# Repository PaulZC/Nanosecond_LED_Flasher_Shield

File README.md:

# Nanosecond LED Flasher Shield
 
A nanosecond LED flasher which provides digital control of both pulse width and LED current. Designed to aid
photomultiplier detector characterisation.

The LED is driven by the new [LMG1025 from Texas Instruments](http://www.ti.com/product/LMG1025-Q1).
Designed for automotive LIDAR applications, this gate driver has typical rise and fall times of 650ps
and 850ps and can produce 5V pulse widths as short as 1.25ns.

The pulse width is controlled by a [Maxim Integrated DS1023S-25+](https://www.maximintegrated.com/en/products/analog/clock-generation-distribution/DS1023.html)
programmable timing element which can produce digitally-adjustable pulse widths of 0 to ~64ns in 0.25ns increments.

The LED current is set by five surface mount resistors connected in series, four of which can be shorted
out by [Toshiba TLP3475 photorelays](https://toshiba.semicon-storage.com/ap-en/semiconductor/product/optoelectronics/photorelay-mosfet-output/detail.TLP3475.html)
allowing the LED current to be adjusted digitally in 16 increments.

The shield also uses a [u-blox MAX-M8Q GNSS module](https://www.u-blox.com/en/product/max-m8-series) as a
signal generator to dictate the flash rate. The flash rate can be set to any frequency between 0.25Hz
and 10MHz.

The shield is designed to be mounted on a [5V ATmega328 Arduino Uno or similar](https://www.sparkfun.com/products/13975).
(Please note that the shield requires 5V I/O signals for correct operation and will not work if mounted
on a 3.3V Arduino Zero or similar.)

## Example Performance

In the image below:
- the yellow trace shows the anode voltage of a Bivar UV3TZ-400-15 UV LED being driven by the shield at maximum brightness (equivalent series resistance approx. 14 ohms) (1V per division)
- the green trace shows the corresponding fast output of a SensL J-series silicon photomultiplier (50mV per division)
- the timebase is 2 nsec per division

The overlapping yellow traces show the LED pulse width being increased in 0.25 nsec increments. The corresponding green traces show how the peak output of
the SiPM increases in line with the LED pulse width and the number of photons emitted during each pulse.

## Repository Contents

- **/Documentation** - Documentation for the hardware and software
- **/Hardware** - BOM, schematic and Eagle PCB design files
- **/Software** - Arduino code
- **LICENSE.md** contains the licence information

## Documentation

- [Hardware overview](https://github.com/PaulZC/Nanosecond_LED_Flasher_Shield/blob/master/Documentation/Hardware/README.md): an overview of the hardware
- [Software user guide](https://github.com/PaulZC/Nanosecond_LED_Flasher_Shield/blob/master/Documentation/Software/README.md): a user guide for the Arduino code

Enjoy!

**_Paul_**

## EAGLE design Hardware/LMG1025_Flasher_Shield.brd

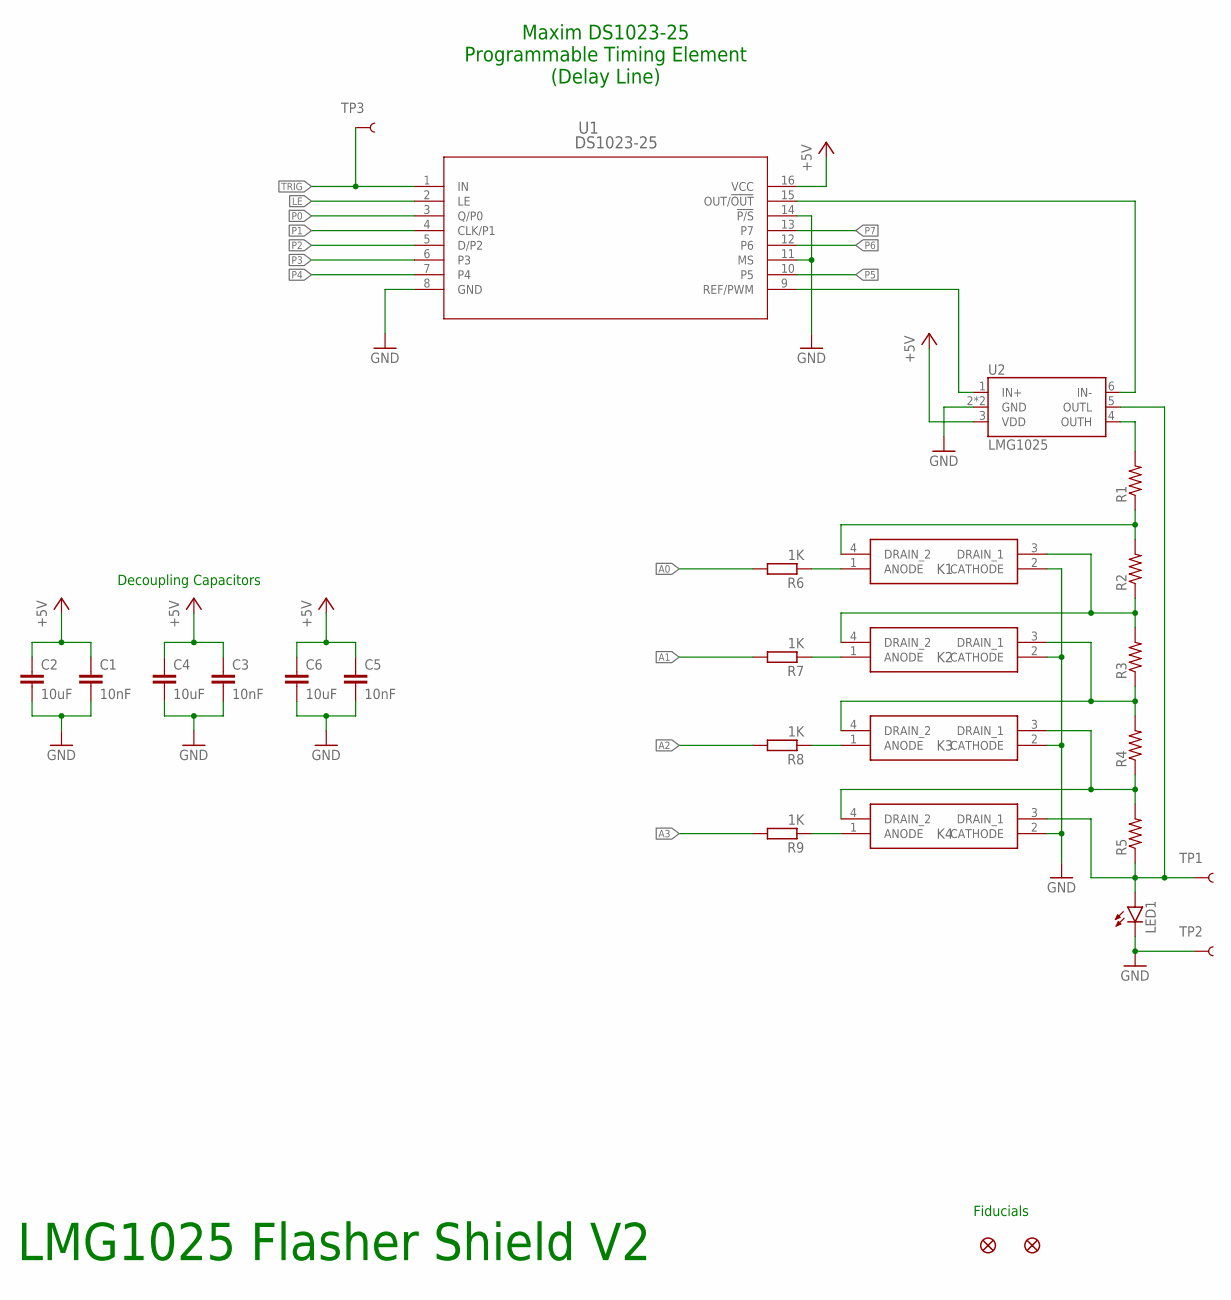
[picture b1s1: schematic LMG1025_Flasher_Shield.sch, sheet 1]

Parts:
C1, C3, C5: 10nF; C0805
C2, C4, C6: 10uF; C0805
FD1, FD2: FIDUCIAL1X2; FIDUCIAL-1X2
K1, K2, K3, K4: TLP3475R(TP,F; TLP3475RTPF
LED1: LED3MM
R1, R2, R3, R4, R5: RESISTOR0805-RES; 0805
R6, R7, R8, R9: 1K; R0603
TP1, TP2, TP3: TEST-POINTPOGO_PTH; 1X01_NO_SILK
U1: DS1023-25; 21-0042B_16
U2: LMG1025

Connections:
+5V: C1.1, C2.1, C3.1, C4.1, C5.1, C6.1, U1.16 (VCC), U2.3 (VDD); also elsewhere on the board
A0: R6.2; also elsewhere on the board
A1: R7.2; also elsewhere on the board
A2: R8.2; also elsewhere on the board
A3: R9.2; also elsewhere on the board
GND: C1.2, C2.2, C3.2, C4.2, C5.2, C6.2, K1.2 (CATHODE), K2.2 (CATHODE), K3.2 (CATHODE), K4.2 (CATHODE), LED1.K (C), TP2.1, U1.8 (GND), U1.11 (MS), U1.14 (!P/S), U2.2 (GND), U2.PAD (GND); also elsewhere on the board
LE: U1.2 (LE); also elsewhere on the board
unnamed: K1.4 (DRAIN_2), R1.1, R2.2
unnamed: K1.3 (DRAIN_1), K2.4 (DRAIN_2), R2.1, R3.2
unnamed: K4.3 (DRAIN_1), LED1.A, R5.1, TP1.1, U2.5 (OUTL)
unnamed: K2.3 (DRAIN_1), K3.4 (DRAIN_2), R3.1, R4.2
unnamed: K3.3 (DRAIN_1), K4.4 (DRAIN_2), R4.1, R5.2
unnamed: R1.2, U2.4 (OUTH)
unnamed: K1.1 (ANODE), R6.1
unnamed: K2.1 (ANODE), R7.1
unnamed: K3.1 (ANODE), R8.1
unnamed: K4.1 (ANODE), R9.1
unnamed: U1.9 (REF/PWM), U2.1 (IN+)
unnamed: U1.15 (OUT/!OUT), U2.6 (IN-)
P0: U1.3 (Q/P0); also elsewhere on the board
P1: U1.4 (CLK/P1); also elsewhere on the board
P2: U1.5 (D/P2); also elsewhere on the board
P3: U1.6 (P3); also elsewhere on the board
P4: U1.7 (P4); also elsewhere on the board
P5: U1.10 (P5); also elsewhere on the board
P6: U1.12 (P6); also elsewhere on the board
P7: U1.13 (P7); also elsewhere on the board
TRIG: TP3.1, U1.1 (IN); also elsewhere on the board

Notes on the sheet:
LMG1025 Flasher Shield V2
Fiducials
Decoupling Capacitors
Maxim DS1023-25 Programmable Timing Element (Delay Line)

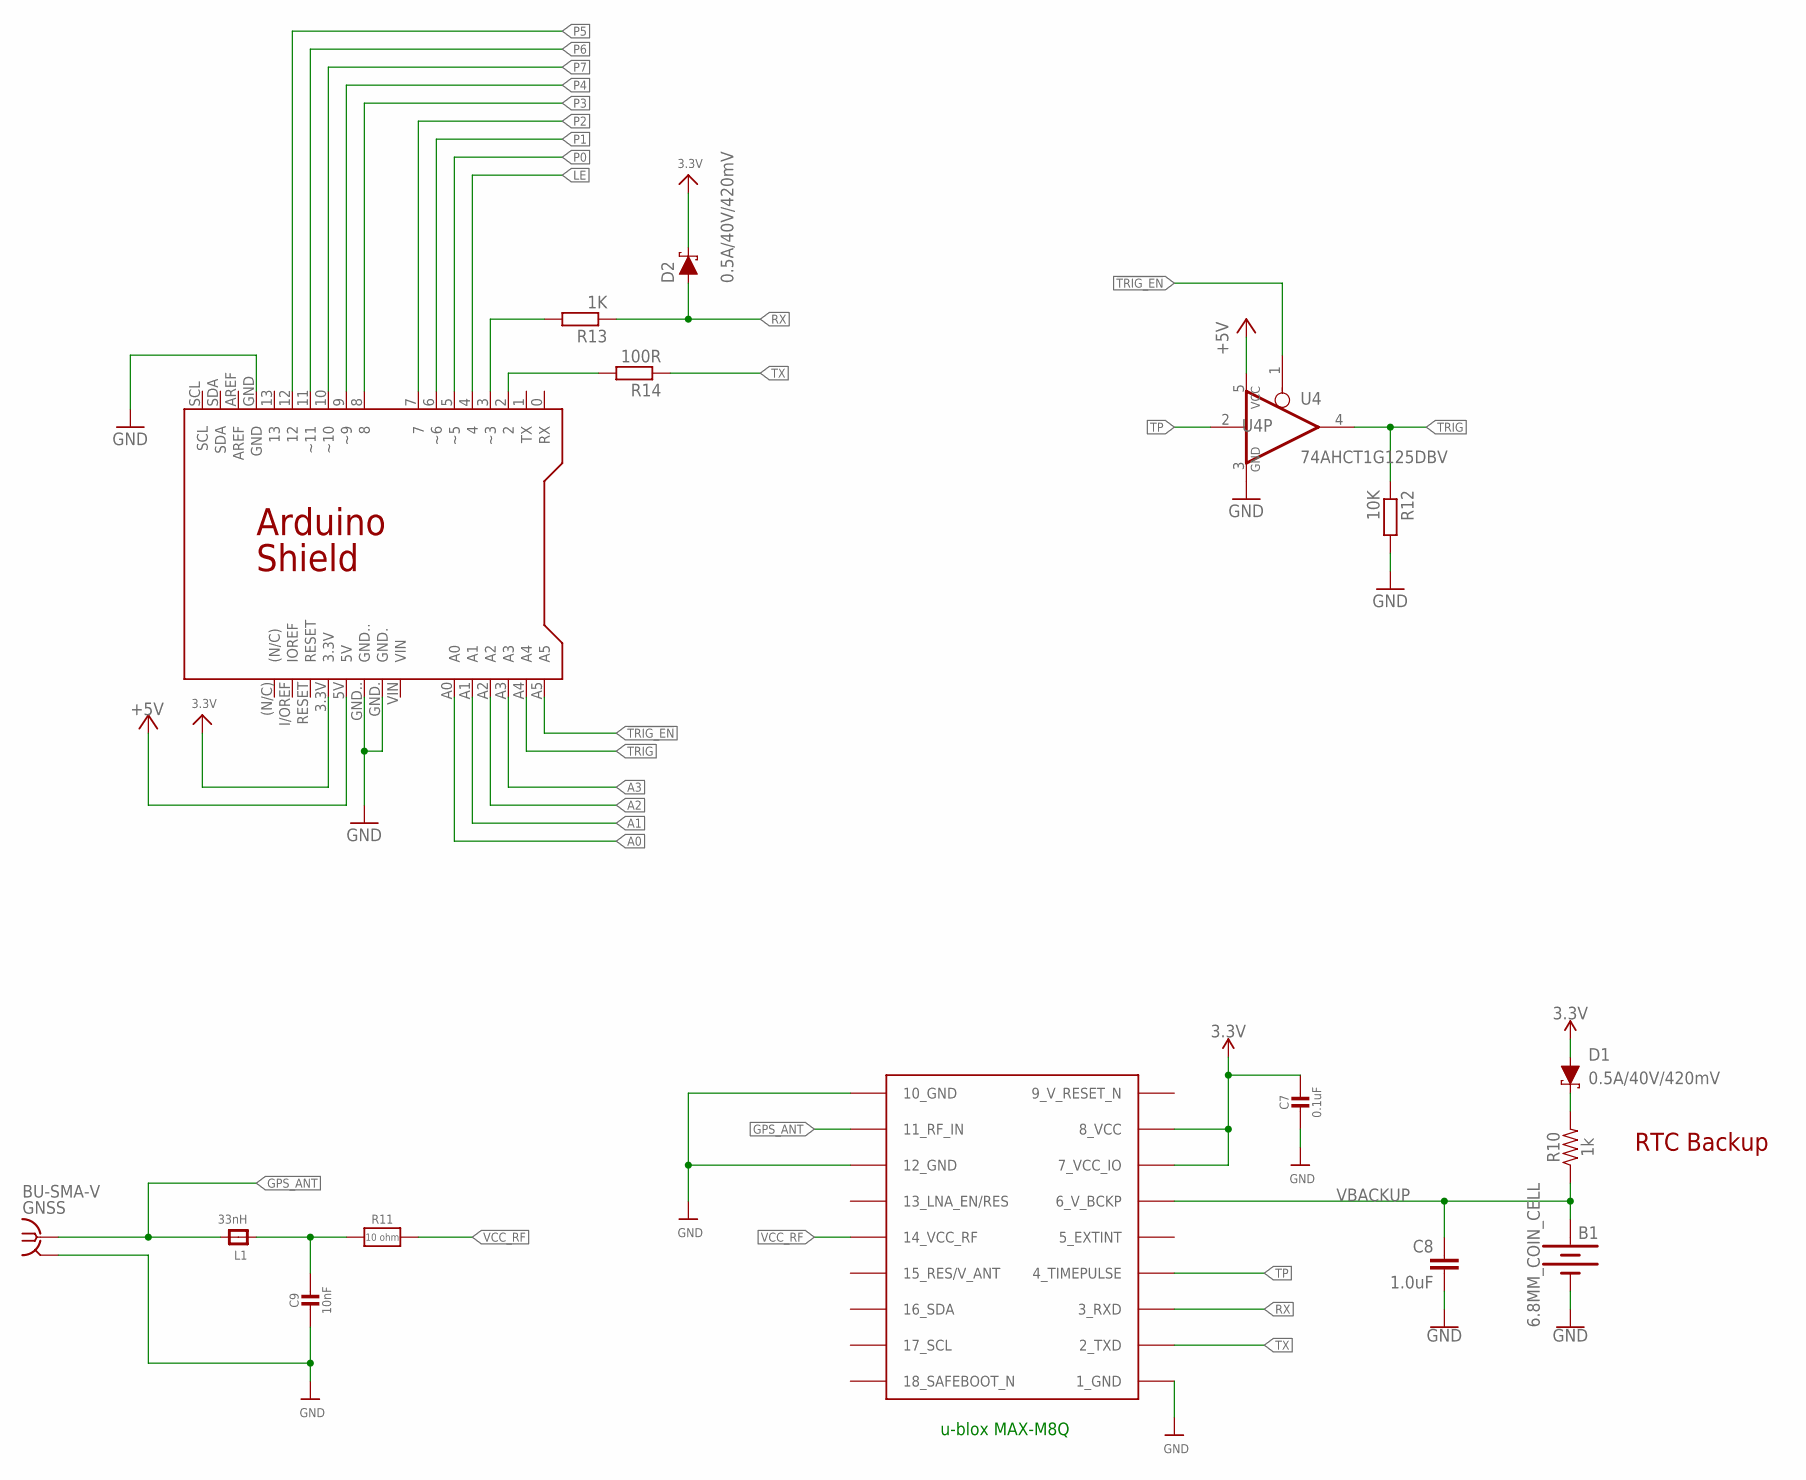
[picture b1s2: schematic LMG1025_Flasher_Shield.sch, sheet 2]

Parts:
B1: 6.8MM_COIN_CELL; BATTCON-6.8MM
C7: 0.1uF; 0805-NO
C8: 1.0uF; 0603
C9: 10nF; 0805-NO
D1, D2: 0.5A/40V/420mV; SOD-323
GNSS: BU-SMA-V
L1: 33nH; 0805-NO
PCB1: CHEC_LED_DRIVER_SHIELD
R10: 1k; 0603@1
R11: 10 ohm; 0805-NO
R12: 10K; R0603
R13: 1K; R0603
R14: 100R; R0603
U3: MAX-M8
U4: 74AHCT1G125DBV; SOT23-5

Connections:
3.3V: C7.1, D1.A, D2.C, PCB1.3.3V, U3.7_VCC_IO, U3.8_VCC
9_V_RESET_N: U3.9_RESET_N (9_V_RESET_N)
!TRIG_EN: PCB1.A5, U4.1 (OE)
+5V: PCB1.5V, U4.5 (VCC); also elsewhere on the board
A0: PCB1.A0; also elsewhere on the board
A1: PCB1.A1; also elsewhere on the board
A2: PCB1.A2; also elsewhere on the board
A3: PCB1.A3; also elsewhere on the board
GND: B1.-, C7.2, C8.2, C9.2, GNSS.2, GNSS.3 (2), GNSS.4 (2), GNSS.5 (2), PCB1.GND, PCB1.GND., PCB1.GND.., R12.2, U3.1_GND, U3.10_GND, U3.12_GND, U4.3 (GND); also elsewhere on the board
GPS_ANT: GNSS.1, L1.2, U3.11_RF_IN
LE: PCB1.4; also elsewhere on the board
unnamed: PCB1.3 (~3), R13.2
unnamed: C9.1, L1.1, R11.1
unnamed: D1.C, R10.2
unnamed: PCB1.2, R14.2
P0: PCB1.5 (~5); also elsewhere on the board
P1: PCB1.6 (~6); also elsewhere on the board
P2: PCB1.7; also elsewhere on the board
P3: PCB1.8; also elsewhere on the board
P4: PCB1.9 (~9); also elsewhere on the board
P5: PCB1.12; also elsewhere on the board
P6: PCB1.11 (~11); also elsewhere on the board
P7: PCB1.10 (~10); also elsewhere on the board
RX: D2.A, R13.1, U3.3_RXD
TP: U3.4_TIMEPULSE, U4.2 (I)
TRIG: PCB1.A4, R12.1, U4.4 (O); also elsewhere on the board
TX: R14.1, U3.2_TXD
VBACKUP: B1.+, C8.1, R10.1, U3.6_V_BCKP
VCC_RF: R11.2, U3.14_VCC_RF

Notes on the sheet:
u-blox MAX-M8Q
RTC Backup

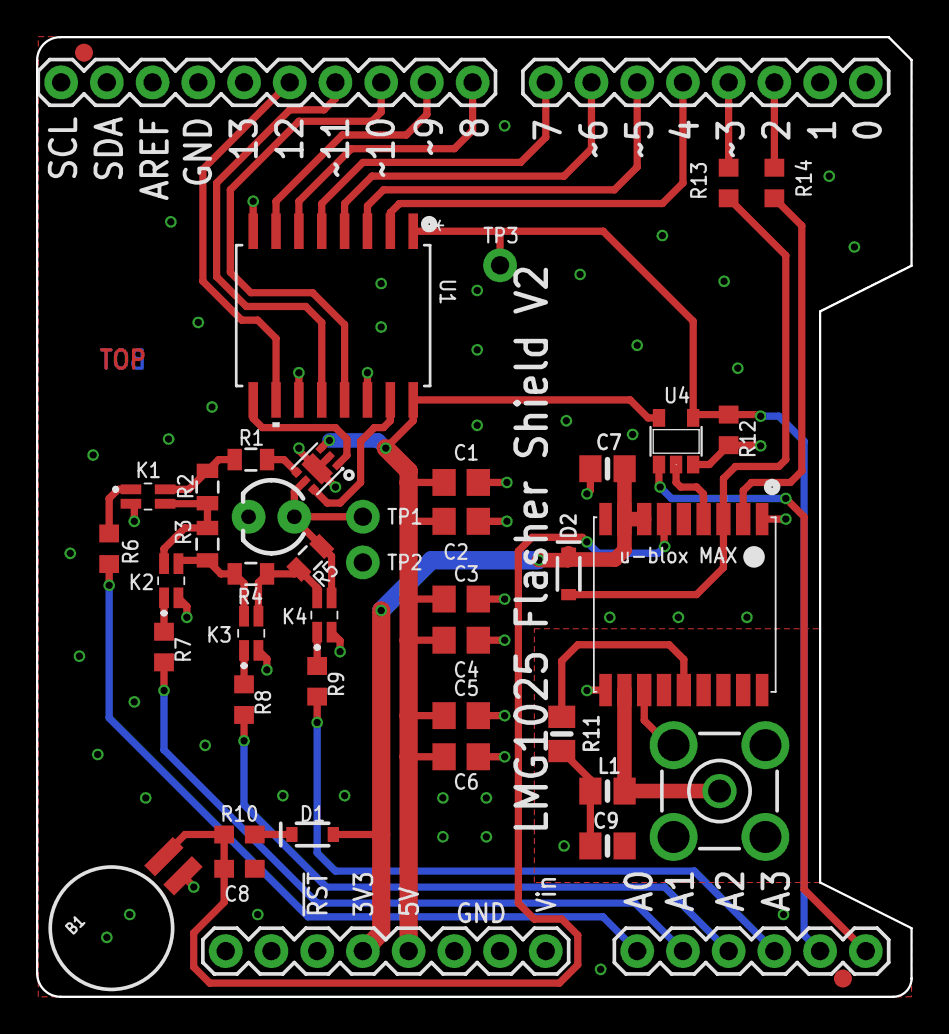
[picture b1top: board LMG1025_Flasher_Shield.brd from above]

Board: 2 copper layers, 48.6 x 53.3 mm, 43 parts (0 on the bottom side), 40 nets.

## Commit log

2020-03-06 Added brief documentation for the software
2020-03-06 Typo correction
2020-03-27 Added the BOM
2020-03-27 Added the LED and SiPM waveforms

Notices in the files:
parts and their libraries:
SparkFun-Aesthetics: Licensing: Creative Commons ShareAlike 4.0 International - https://creativecommons.org/licenses/by-sa/4.0
